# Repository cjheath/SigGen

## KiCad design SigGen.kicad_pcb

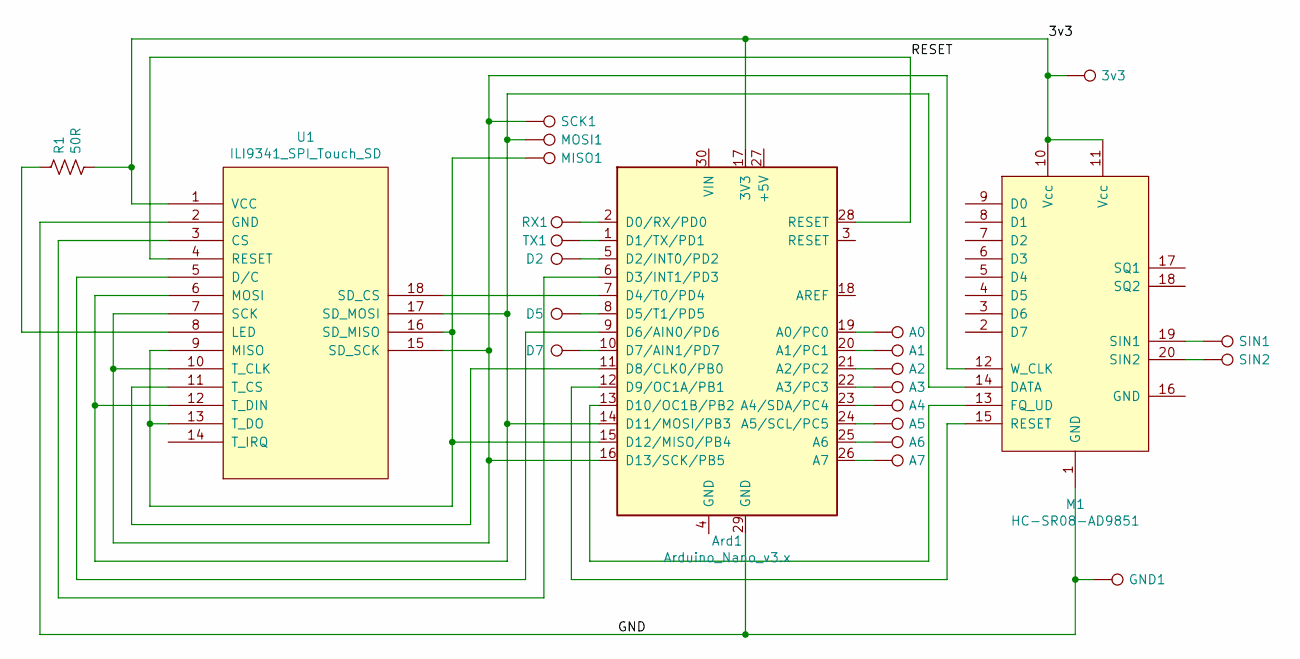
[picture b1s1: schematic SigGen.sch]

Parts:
3v3: TestPoint; Testpoint
A0, A1, A2, A3, A4, A5, A6, A7: TestPoint; Testpoint
Ard1: Arduino_Nano_v3.x; Arduino_Nano
D2, D5, D7: TestPoint; Testpoint
GND1: TestPoint; Testpoint
M1: HC-SR08-AD9851
MISO1: TestPoint; Testpoint
MOSI1: TestPoint; Testpoint
R1: 50R; R_0805_2012Metric_Pad1.15x1.40mm_HandSolder
RX1: TestPoint; Testpoint
SCK1: TestPoint; Testpoint
SIN1, SIN2: TestPoint; Testpoint
TX1: TestPoint; Testpoint
U1: ILI9341_SPI_Touch_SD; TJCTM24024-SPI

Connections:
/3v3: 3v3.1, Ard1.17 (3V3), M1.10 (Vcc), M1.11 (Vcc), R1.2, U1.1 (VCC)
/GND: Ard1.29 (GND), GND1.1, M1.1 (GND), U1.2 (GND)
/RESET: Ard1.28 (RESET), U1.4 (RESET)
unnamed: A0.1, Ard1.19 (A0/PC0)
unnamed: A1.1, Ard1.20 (A1/PC1)
unnamed: A2.1, Ard1.21 (A2/PC2)
unnamed: A3.1, Ard1.22 (A3/PC3)
unnamed: A4.1, Ard1.23 (A4/SDA/PC4)
unnamed: A5.1, Ard1.24 (A5/SCL/PC5)
unnamed: A6.1, Ard1.25 (A6)
unnamed: A7.1, Ard1.26 (A7)
unnamed: Ard1.1 (D1/TX/PD1), TX1.1
unnamed: Ard1.2 (D0/RX/PD0), RX1.1
unnamed: Ard1.5 (D2/INT0/PD2), D2.1
unnamed: Ard1.6 (D3/INT1/PD3), U1.3 (CS)
unnamed: Ard1.7 (D4/T0/PD4), U1.18 (SD_CS)
unnamed: Ard1.8 (D5/T1/PD5), D5.1
unnamed: Ard1.9 (D6/AIN0/PD6), U1.5 (D/C)
unnamed: Ard1.10 (D7/AIN1/PD7), D7.1
unnamed: Ard1.11 (D8/CLK0/PB0), U1.11 (T_CS)
unnamed: Ard1.12 (D9/OC1A/PB1), M1.15 (RESET)
unnamed: Ard1.13 (D10/OC1B/PB2), M1.13 (FQ_UD)
unnamed: Ard1.14 (D11/MOSI/PB3), M1.14 (DATA), MOSI1.1, U1.6 (MOSI), U1.12 (T_DIN), U1.17 (SD_MOSI)
unnamed: Ard1.15 (D12/MISO/PB4), MISO1.1, U1.9 (MISO), U1.13 (T_DO), U1.16 (SD_MISO)
unnamed: Ard1.16 (D13/SCK/PB5), M1.12 (W_CLK), SCK1.1, U1.7 (SCK), U1.10 (T_CLK), U1.15 (SD_SCK)
unnamed: M1.19 (SIN1), SIN1.1
unnamed: M1.20 (SIN2), SIN2.1
unnamed: R1.1, U1.8 (LED)

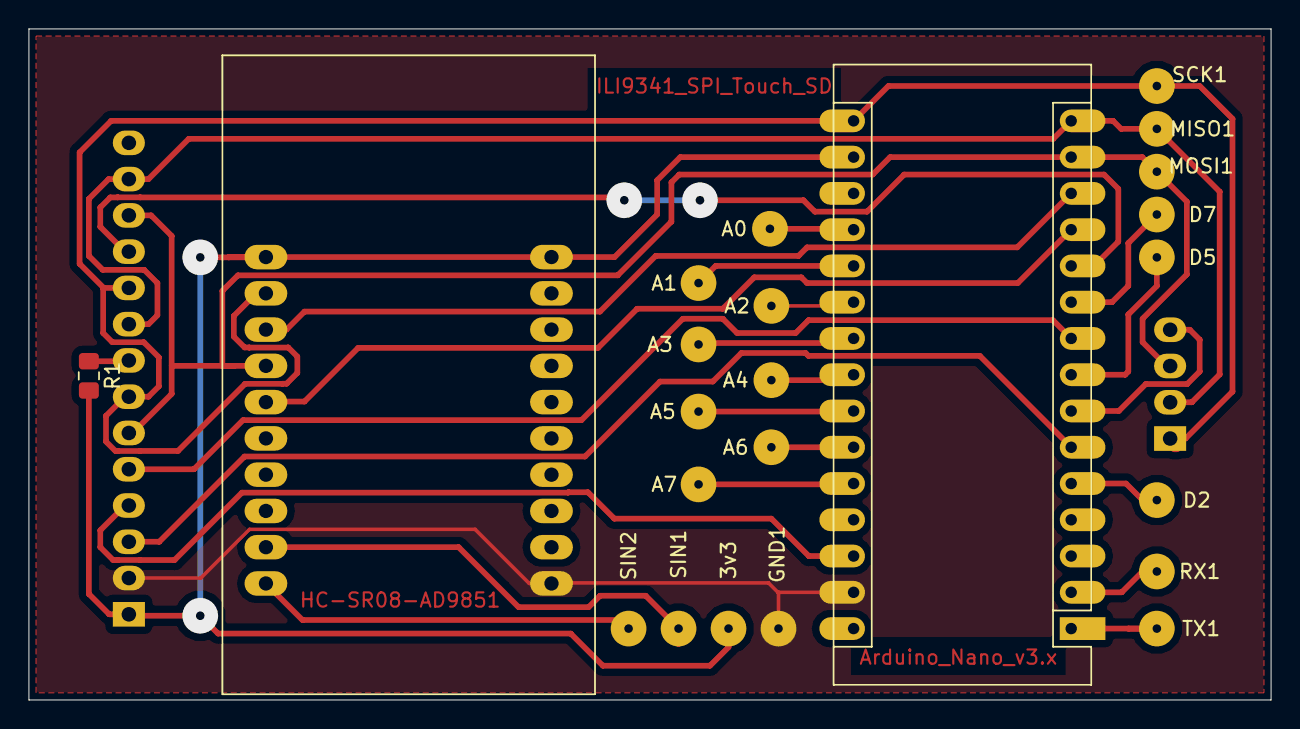
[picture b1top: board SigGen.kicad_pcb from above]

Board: 2 copper layers, 87.0 x 47.0 mm, 24 parts (1 on the bottom side), 28 nets.

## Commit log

2019-03-19 Nano, LCD and AD9851 wired and routed
2019-03-20 Added test points for external wiring
2019-03-21 Updated with ground fills
2019-03-22 Track size increased to 0.4mm
2019-03-26 first prototype made
2020-10-02 Added schematic
